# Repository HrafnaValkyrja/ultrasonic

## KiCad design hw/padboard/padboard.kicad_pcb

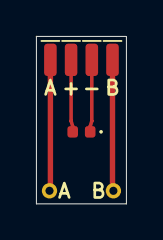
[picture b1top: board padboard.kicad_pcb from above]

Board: 2 copper layers, 5.0 x 9.3 mm, 7 parts (0 on the bottom side), 4 nets.

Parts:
D1: LED_0402_1005Metric
J1, J2, J3, J4: WirePad_SMD_0.7x1.8mm
J5, J6: WirePad_PTH_D0.45mm_Pad0.85mm

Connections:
LED_A: D1.2, J3.1
LED_K: D1.1, J4.1
OUT_A: J1.1, J5.1
OUT_B: J2.1, J6.1

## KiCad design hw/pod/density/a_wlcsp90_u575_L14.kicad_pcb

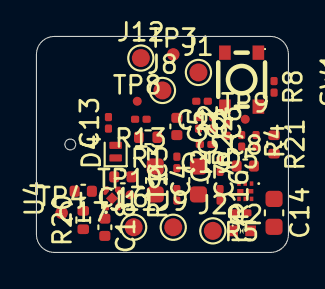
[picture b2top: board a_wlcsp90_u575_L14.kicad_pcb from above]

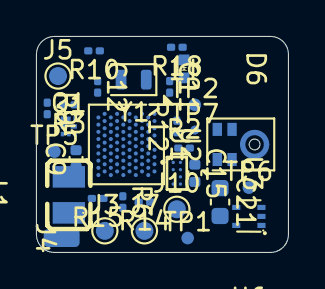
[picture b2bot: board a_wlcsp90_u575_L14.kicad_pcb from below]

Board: 4 copper layers, 14.0 x 12.0 mm, 74 parts (32 on the bottom side), 42 nets, no tracks yet.

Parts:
C1, C2, C3, C6, C10, C11, C12, C13, C19, C22: C_0201_0603Metric
C4, C7, C14, C21: C_0603_1608Metric
C5, C8, C9, C15, C16, C17, C18: C_0402_1005Metric
D4: D_SOD-882
D5, D6: X1SON-2_L1.0-W0.6-P0.65-BI-1
J1, J2, J3, J5, J7, J8, J9, J10, J11, J12: TestPoint_Pad_D1.0mm
J4: WirePad_1.0x2.0mm
L1: L0806
Q1, Q2: Nexperia_SOT1216_DFN1010B-6
R1, R20, R21: R_0402_1005Metric
R2, R3, R4, R5, R6, R8, R9, R10, R12, R13, R14, R15, R16, R18, R22: R_0201_0603Metric
RT1: R_0201_0603Metric
SW1: SW-SMD_4P-L3.0-W2.6-P1.85-LS3.4
TP1, TP2, TP3, TP4, TP5, TP6: TestPoint_Pad_D0.7mm
TP7, TP8, TP9, TP10: TestDot_D0.5mm
U1: ST_WLCSP-90_4.2x3.95mm_Layout18x10_P0.4mm_Stagger
U2: Knowles_LGA-5_3.5x2.65mm; Knowles_LGA-5_3.5x2.65mm_Port0.6
U3: DSBGA-8_L1.6-W0.9-R2-C4-P0.40-BL
U4: X2SON-4_L1.0-W1.0-P0.65-TL-EP
U6: SOT-553-5_L1.6-W1.2-P0.50-LS1.6-TL-1
Y1: Crystal_SMD_2012-2Pin_2.0x1.2mm

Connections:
+3V0: C1.1, C2.1, C3.1, C4.1, C5.1, C6.1, C7.1, C14.1, Q1.4, Q2.4, R3.2, R5.2, R15.2, R16.2, R20.2, SW1.1, SW1.2, TP4.1, U1.A1, U1.B2, U1.B16, U1.H2, U1.J17, U1.K14
BRIDGE_RTN: Q1.1, Q2.1, R21.1, R22.1
BTN: R10.1, SW1.3, SW1.4, U1.J1
CC: D6.1, J12.1, R18.1
CHG_INT: U1.B14, U3.A1
DBG_TX: TP7.1, U1.B10
DOCK_VBUS: D4.2, D5.1, J3.1
GA_N: Q1.2, R4.1, U1.K8
GA_P: Q1.5, R3.1, U1.F16
GB_N: Q2.2, R6.1, U1.F18
GB_P: Q2.5, R5.1, U1.D18
GND: C1.2, C2.2, C3.2, C4.2, C5.2, C6.2, C7.2, C8.2, C9.2, C10.2, C11.2, C12.2, C13.2, C14.2, C15.2, C16.2, C17.2, C18.2, C19.2, C21.2, C22.2, D5.2, D6.2, J4.1, R1.2, R4.2, R6.2, R9.2, R10.2, R13.2, R18.2, R21.2, RT1.2, TP5.1, U1.A3, U1.A11, U1.A17, U1.D10, U1.E9, U1.E11, U1.F8, U1.F10, U1.G3, U1.G9, U1.J13, U1.K18, U2.2, U2.3, U3.D2, U4.2, U4.5, U6.4
I2C_SCL: R15.1, U1.H18, U3.B1
I2C_SDA: R16.1, U1.G17, U3.C1
I_SENSE: C22.1, R22.2, U1.J7
LDO_OUT: C18.1, R20.1, U4.1
LED_A: J7.1, R14.2
LED_K: J8.1, U1.A9
LSE_IN: C11.1, U1.D2, Y1.1
LSE_OUT: C12.1, U1.E1, Y1.2
MDF_CCK: TP8.1, U1.A5
MDF_SDI: TP9.1, U1.K10
MIC_CLK: R2.2, U2.4
MIC_DATA: TP10.1, U1.B12, U2.1
MIC_VDD: C13.1, U1.K6, U2.5
unnamed: R1.1, U1.A7
unnamed: R2.1, U1.A13
NRST: C10.1, TP3.1, U1.G1
OUT_A: J1.1, Q1.3, Q1.6, Q1.7, Q1.8
OUT_B: J2.1, Q2.3, Q2.6, Q2.7, Q2.8
SWCLK: TP2.1, U1.A15
SWDIO: TP1.1, U1.B18
TS: J9.1, RT1.1, U1.J3, U3.D1
USB_DM: J11.1, U1.D16, U6.5
USB_DP: J10.1, U1.C17, U6.3
VBAT: C16.1, J5.1, R8.1, U3.C2
VBAT_SENSE: C19.1, R8.2, R9.1, U1.J5
VBUS: C15.1, D4.1, R12.1, U3.A2
VBUS_SENSE: R12.2, R13.1, U1.K2
VDD11: C8.1, C9.1, L1.2, U1.B6, U1.K16
VLXSMPS: L1.1, U1.K12
VSYS: C17.1, C21.1, R14.1, TP6.1, U3.B2, U4.3, U4.4

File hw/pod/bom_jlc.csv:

Comment,Designator,Footprint,LCSC Part #,Qty,In sourcing lock
100n,"C1,C10,C13,C19,C2,C3,C6",C_0402_1005Metric,C1525,7,yes
15p,"C11,C12",C_0402_1005Metric,C1548,2,yes
22u,C14,C_0603_1608Metric,C59461,1,yes
4u7 25V,C15,C_0402_1005Metric,C2858031,1,dated lookup
4u7,C16,C_0402_1005Metric,C23733,1,yes
10n,C22,C_0402_1005Metric,C15195,1,dated lookup
10u,"C21,C4,C7",C_0603_1608Metric,C19702,3,yes
1u,"C17,C18,C5",C_0402_1005Metric,C52923,3,yes
2u2 10V,"C8,C9",C_0402_1005Metric,C107369,2,yes
1N5819WS,D4,D_SOD-323,C191023,1,yes
TPD1E10B06DPYR,"D5,D6",X1SON-2_L1.0-W0.6-P0.65-BI-1,C48260,2,yes
2u2,L1,L0806,C337891,1,yes
PMCXB290UE,"Q1,Q2",Nexperia_SOT1216_DFN1010B-6,C19654206,2,yes
10k,"R1,R15,R16",R_0402_1005Metric,C25744,3,dated lookup
2k2,"R10,R14",R_0402_1005Metric,C25879,2,dated lookup
5k1,R18,R_0402_1005Metric,C25905,1,dated lookup
33,R2,R_0402_1005Metric,C25105,1,dated lookup
0,R20,R_0402_1005Metric,C17168,1,dated lookup
0.1,R21,R_1206_3216Metric,C25334,1,dated lookup
1k,R22,R_0402_1005Metric,C11702,1,dated lookup
100k,"R12,R13,R3,R4,R5,R6",R_0402_1005Metric,C25741,6,yes
1M,"R8,R9",R_0402_1005Metric,C26083,2,dated lookup
10k B3435,RT1,R_0402_1005Metric,C77131,1,dated lookup
KMT022NGJLHS,SW1,SW-SMD_4P-L3.0-W2.6-P1.85-LS3.4,C221707,1,dated lookup
STM32U575CIUxQ,U1,QFN-48-1EP_7x7mm_P0.5mm_EP5.6x5.6mm,C5271013,1,dated lookup
SPH0641LU4H-1,U2,Knowles_LGA-5_3.5x2.65mm_Port0.6,C2879853,1,dated lookup
BQ25180YBGR,U3,DSBGA-8_L1.6-W0.9-R2-C4-P0.40-BL,C3682423,1,dated lookup
TPS7A2030PDQNR,U4,X2SON-4_L1.0-W1.0-P0.65-TL-EP,C5220164,1,yes
TPD2E2U06DRLR,U6,SOT-553-5_L1.6-W1.2-P0.50-LS1.6-TL-1,C1972959,1,dated lookup
32.768k,Y1,FC-135R_L3.2-W1.5,C32346,1,yes
